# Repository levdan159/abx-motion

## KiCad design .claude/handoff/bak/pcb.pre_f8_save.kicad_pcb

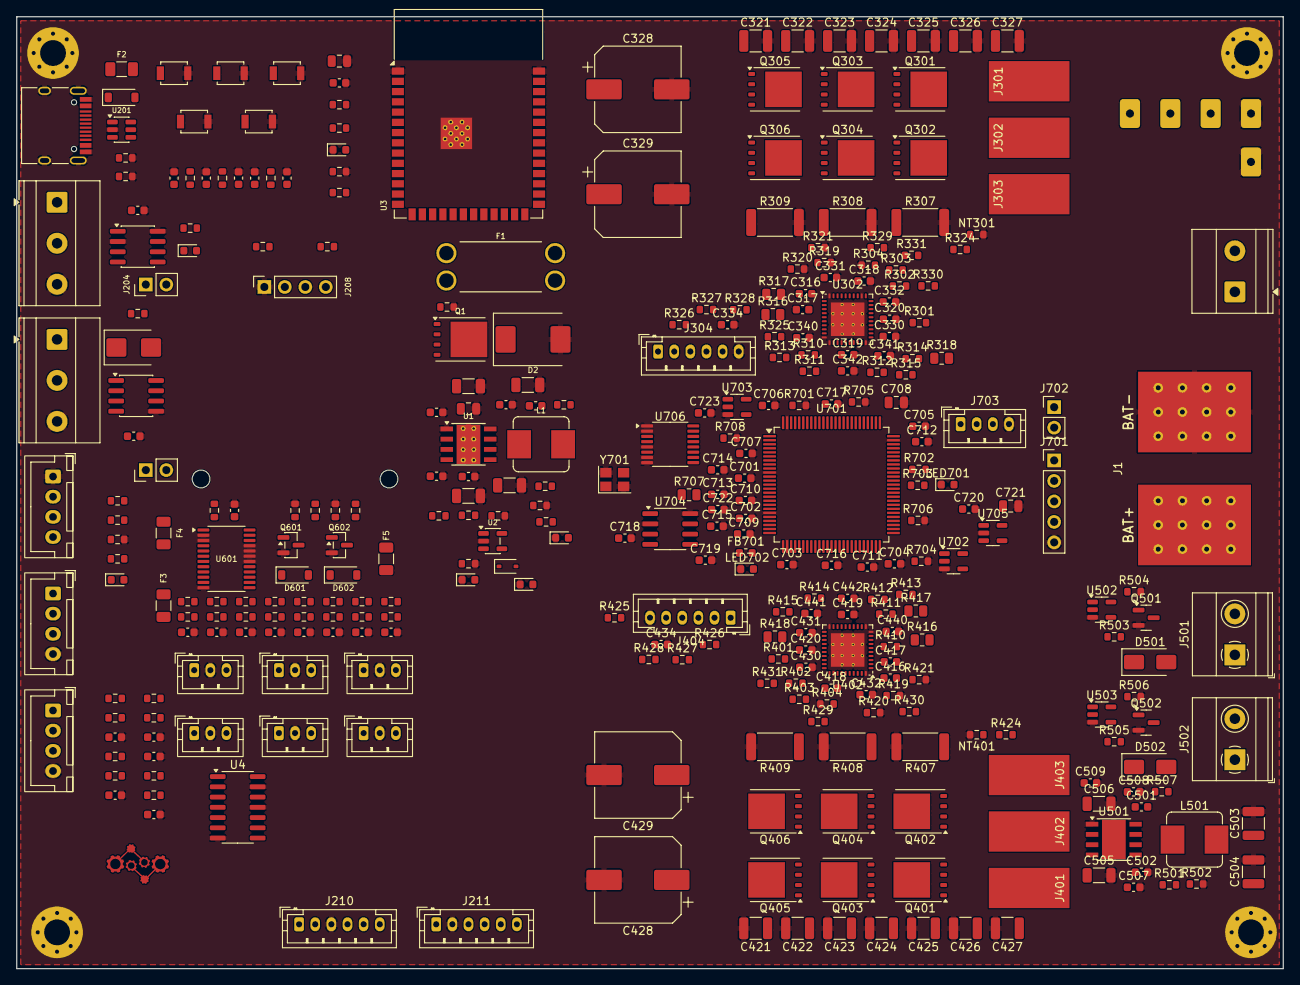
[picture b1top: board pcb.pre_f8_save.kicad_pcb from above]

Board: 4 copper layers, 157.0 x 118.0 mm, 344 parts (1 on the bottom side), 224 nets, no tracks yet.

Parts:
C1, C6, C202, C203, C204, C209, C210, C211, C212, C213, C214, C319, C419, C501, C508, C509, C601, C701, C702, C703, C704, C705, C706, C707, C709, C715, C716, C717, C718, C719, C722, C723: 100nF; C_0603_1608Metric
C2, C3, C505, C506: 4.7uF/100V; C_1206_3216Metric
C4, C320, C420, C507: 100nF/100V; C_0603_1608Metric
C5, C9, C318, C418, C502, C710, C720: 1uF; C_0603_1608Metric
C7, C8: 22uF; C_1206_3216Metric
C10, C201, C721: 10uF; C_0805_2012Metric
C205, C206, C207, C208, C340, C341, C342, C440, C441, C442: 1nF; C_0603_1608Metric
C316, C416: 47nF/100V; C_0603_1608Metric
C317, C417: 1uF/25V; C_0603_1608Metric
C321, C322, C323, C324, C325, C326, C327, C421, C422, C423, C424, C425, C426, C427: 10uF/100V; C_1210_3225Metric
C328, C329, C428, C429: 220uF/63V; CP_Elec_10x10.5
C330, C331, C332, C430, C431, C432: 2.2nF; C_0603_1608Metric
C334, C434, C602, C603, C604, C605, C606, C607, C608, C609: 10nF; C_0603_1608Metric
C503, C504: 22uF/50V; C_1210_3225Metric
C708: 4.7uF; C_0805_2012Metric
C711, C712: 2.2uF; C_0603_1608Metric
C713, C714: 18pF; C_0603_1608Metric
D1: BZT52C12S; D_SOD-323
D2: SMCJ43A; D_SMC
D201: SMBJ6.5CA; D_SMB
D202, D601, D602: B5819W; D_SOD-123
D501, D502: SS34; D_SMA
F1: 5A; Fuseholder_Keystone_3557-2
F2, F3, F5: 500mA_PTC; Fuse_1206_3216Metric
F4: 250mA_PTC; Fuse_1206_3216Metric
FB701: 600R@100MHz; L_0603_1608Metric
H1, H2, H3, H4: M3_Mount; MountingHole_3.2mm_M3_Pad_Via
H5, H6: M2_OLED; MountingHole_2.2mm_M2
J1: BATTERY_IN; ABX_BatteryPads_1x02_SMD_10x14mm_P14mm
J102: E_STOP; TerminalBlock_Phoenix_MKDS-1,5-2-5.08_1x02_P5.08mm_Horizont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
J201: USB-C; USB_C_Receptacle_HRO_TYPE-C-31-M-12
J202: ENC1_CONN; JST_XH_B4B-XH-A_1x04_P2.50mm_Vertical
J203: ENC2_CONN; JST_XH_B4B-XH-A_1x04_P2.50mm_Vertical
J204: CAN_TERM; PinHeader_1x02_P2.54mm_Vertical
J205: CAN_BUS; TerminalBlock_Phoenix_MKDS-1,5-3-5.08_1x03_P5.08mm_Horizont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
J206: RS485_TERM; PinHeader_1x02_P2.54mm_Vertical
J207: RS485_BUS; TerminalBlock_Phoenix_MKDS-1,5-3-5.08_1x03_P5.08mm_Horizont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
J208: OLED_I2C; PinSocket_1x04_P2.54mm_Vertical
J209: I2C_EXP; JST_XH_B4B-XH-A_1x04_P2.50mm_Vertical
J210: GPS; JST_PH_B6B-PH-K_1x06_P2.00mm_Vertical
J211: IMU; JST_PH_B6B-PH-K_1x06_P2.00mm_Vertical
J301, J401: PHASE_A; SolderWirePad_1x01_SMD_5x10mm
J302, J402: PHASE_B; SolderWirePad_1x01_SMD_5x10mm
J303, J403: PHASE_C; SolderWirePad_1x01_SMD_5x10mm
J304, J404: HALL_TEMP; JST_PH_B6B-PH-K_1x06_P2.00mm_Vertical
J501: BRAKE1; TerminalBlock_Phoenix_MKDS-1,5-2-5.08_1x02_P5.08mm_Horizont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
J502: BRAKE2; TerminalBlock_Phoenix_MKDS-1,5-2-5.08_1x02_P5.08mm_Horizont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
J601, J602, J603, J604, J605, J606: B3B-PH-K-S; JST_PH_B3B-PH-K_1x03_P2.00mm_Vertical
J701: SWD; PinHeader_1x05_P2.54mm_Vertical
J702: BOOT; PinHeader_1x02_P2.54mm_Vertical
J703: UART; JST_PH_B4B-PH-K_1x04_P2.00mm_Vertical
L1: 15uH; L_Bourns_SRP7028A_7.3x6.6mm
L501: 47uH 3A; L_Bourns_SRP7028A_7.3x6.6mm
LED201: LED_YEL_CAN; LED_0603_1608Metric
LED202: LED_YEL_485; LED_0603_1608Metric
LED203: LED_BLU_STAT; LED_0603_1608Metric
LED701: LED_GRN; LED_0603_1608Metric
LED702: LED_RED; LED_0603_1608Metric
LED_PWR_3V3_1, LED_PWR_5V1: LED_GRN; LED_0603_1608Metric
LED_PWR_BATT1: LED_GRN; LED_0603_1608Metric
LOGO1: ABX_Logo_Gears_Gold
LOGO2: ABX_Text_Gold
NT301, NT401: NTC 10k B3435; R_0603_1608Metric
Q1: SQJ459EP-T1_GE3; TDSON-8-1
Q301, Q302, Q303, Q304, Q305, Q306, Q401, Q402, Q403, Q404, Q405, Q406: CSD19532Q5B; TDSON-8-1
Q501, Q502: SI2318CDS; SOT-23
Q601, Q602: AO3400A; SOT-23
R1: 47k; R_0603_1608Metric
R2, R4, R501, R504, R506, R706: 100k; R_0603_1608Metric
R3: 6.8k; R_0603_1608Metric
R5: 24.9k; R_0603_1608Metric
R6: 22k; R_0603_1608Metric
R7, R8, R212, R214, R216, R218, R220, R224, R230, R326, R327, R328, R426, R427, R428, R507, R609, R610, R611, R612, R613, R614, R615, R616, R617, R618, R702, R703: 1k; R_0603_1608Metric
R9, R203, R206, R227, R228, R229, R231, R232, R301, R302, R303, R304, R324, R325, R401, R402, R403, R404, R424, R425, R701, R704, R705: 10k; R_0603_1608Metric
R201, R202: 5.1k; R_0603_1608Metric
R211, R213, R215, R217, R225, R226, R329, R330, R331, R429, R430, R431, R601, R602, R603, R604, R605, R606, R607, R608: 4.7k; R_0603_1608Metric
R219, R221: 120; R_0603_1608Metric
R222, R223: 330R; R_0603_1608Metric
R307, R308, R309, R407, R408, R409: 1m 3W; R_2512_6332Metric
R310, R311, R312, R313, R314, R315, R410, R411, R412, R413, R414, R415: 2.2; R_0603_1608Metric
R316, R317, R318, R416, R417, R418, R707: 39k; R_0805_2012Metric
R319, R320, R321, R419, R420, R421, R708: 2.2k; R_0603_1608Metric
R502: 4.32k; R_0603_1608Metric
R503, R505: 22; R_0603_1608Metric
R619, R620: 100; R_0603_1608Metric
SW201: RESET; SW_SPST_B3U-1000P
SW202: BOOT; SW_SPST_B3U-1000P
SW203: BTN_BACK; SW_SPST_B3U-1000P
SW204: BTN_NEXT; SW_SPST_B3U-1000P
SW205: BTN_HOME; SW_SPST_B3U-1000P
TP_3V3_1: TP_3V3_1; TestPoint_Pad_D1.5mm
TP_5V1: TP_5V1; TestPoint_Pad_D1.5mm
TP_BATT1: TP_BATT1; TestPoint_Pad_D1.5mm
TP_GND1: TP_GND1; TestPoint_Pad_D1.5mm
TP_GND2: TP_GND2; TestPoint_Pad_D1.5mm
U1: LMR36520FADDA; Texas_HSOP-8-1EP_3.9x4.9mm_P1.27mm_ThermalVias
U2, U705: AP2112K-3.3; SOT-23-5
U3: ESP32-S3-WROOM-1-N8R2; ESP32-S3-WROOM-1
U4: 74LVC14A; SOIC-14_3.9x8.7mm_P1.27mm
U201: USBLC6-2SC6; SOT-23-6
U202: TCAN1042V-Q1; SOIC-8_3.9x4.9mm_P1.27mm
U203: THVD1450DR; SOIC-8_3.9x4.9mm_P1.27mm
U302, U402: DRV8323SRTAR; Texas_RTA0040B_WQFN-40-1EP_6x6mm_P0.5mm_EP4.15x4.15mm
U501: LMR36520FADDA; Texas_HSOP-8-1EP_3.9x4.9mm_P1.27mm
U502, U503, U702, U703: 74LVC1G08; SOT-23-5
U601: PCA9555PW,118; TSSOP-24_4.4x7.8mm_P0.65mm
U701: STM32F405VGT6; LQFP-100_14x14mm_P0.5mm
U704: TCAN1042V; SOIC-8_3.9x4.9mm_P1.27mm
U706: 74HC4051; TSSOP-16_4.4x5mm_P0.65mm
Y701: 8MHz CL12pF; Crystal_SMD_3225-4Pin_3.2x2.5mm

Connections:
+3V3: C10.1, C201.1, C202.1, C209.1, C211.1, C508.1, C509.1, C601.1, F4.1, J102.1, J208.2, J210.2, J211.1, R8.1, R203.1, R206.1, R220.1, R222.1, R224.1, R225.1, R226.1, R227.1, R228.1, R229.1, R232.1, R601.1, R602.1, R603.1, R604.1, R605.1, R606.1, R607.1, R608.1, TP_3V3_1.1 (1_1), U2.5 (VOUT), U3.2 (3V3), U4.14 (VCC), U202.5 (VIO), U203.8 (VCC), U502.5 (VCC), U503.5 (VCC), U601.24 (VDD)
+3V3_ESC: C319.1, C419.1, C701.1, C702.1, C703.1, C704.1, C705.1, C706.1, C707.1, C708.1, C716.1, C717.1, C719.1, C721.1, C723.1, FB701.1, J701.1, J702.2, R301.1, R302.1, R303.1, R324.1, R325.1, R329.1, R330.1, R331.1, R401.1, R402.1, R403.1, R424.1, R425.1, R429.1, R430.1, R431.1, U302.24 (VREF), U402.24 (VREF), U701.6 (VBAT), U701.11 (VDD), U701.19 (VDD), U701.28 (VDD), U701.50 (VDD), U701.75 (VDD), U701.100 (VDD), U702.5 (VCC), U703.5 (VCC), U704.5 (VIO), U705.5 (VOUT), U706.16 (VCC)
+5V: C7.1, C8.1, C9.1, C210.1, C718.1, C720.1, D202.1 (K), F3.1, F5.1, J210.1, J304.1, J404.1, J703.1, L1.2, R4.1, R7.1, R211.1, R213.1, R215.1, R217.1, TP_5V1.1 (1_1), U2.1 (VIN), U2.3 (EN), U202.3 (VCC), U704.3 (VCC), U705.1 (VIN), U705.3 (EN)
+BATT: C2.1, C3.1, C4.1, C505.1, C506.1, C507.1, D1.1 (K), D2.1 (A1), Q1.1 (S), Q1.2 (S), Q1.3 (S), R2.1, R6.1, TP_BATT1.1 (1_1), U1.2 (VIN), U1.3 (EN), U501.2 (VIN), U501.3 (EN)
/+3V3_DRV_EN: J102.2, R9.1, R507.1, R706.1, U502.2, U503.2, U601.17 (IO1_4), U702.2, U703.2
/BRAKE1_EN: U3.19 (IO11), U502.1
/BRAKE2_EN: U3.20 (IO12), U503.1
/Brakes/+24V_BRAKE: C503.1, C504.1, D501.1 (K), D502.1 (K), J501.1, J502.1, L501.2, R501.1
/Brakes/BRK1_COIL_N: D501.2 (A), J501.2, Q501.3 (D)
/Brakes/BRK1_G: R503.1, U502.4
/Brakes/BRK1_GR: Q501.1 (G), R503.2, R504.1
/Brakes/BRK2_COIL_N: D502.2 (A), J502.2, Q502.3 (D)
/Brakes/BRK2_G: R505.1, U503.4
/Brakes/BRK2_GR: Q502.1 (G), R505.2, R506.1
/Brakes/BR_BOOT: C501.1, U501.7 (BOOT)
/Brakes/BR_FB: R501.2, R502.1, U501.5 (FB)
/Brakes/BR_SW: C501.2, L501.1, U501.8 (SW)
/Brakes/BR_VCC: C502.1, U501.6 (VCC)
/CAN_H: J204.1, J205.1, U202.7 (CANH), U704.7 (CANH)
/CAN_L: J205.2, R219.2, U202.6 (CANL), U704.6 (CANL)
/DRV_SCLK: U302.28 (SCLK), U402.28 (SCLK), U701.78 (PC10)
/DRV_SDI: U302.27 (SDI), U402.27 (SDI), U701.80 (PC12)
/DRV_SDO: R302.2, R402.2, U302.26 (SDO), U402.26 (SDO), U701.79 (PC11)
/ESC_MCU/ADC_MUX: U701.29 (PA4), U706.3 (A)
/ESC_MCU/BOOT0: J702.1, R701.1, U701.94 (BOOT0)
/ESC_MCU/CAN_RX: U701.81 (PD0), U704.4 (RXD)
/ESC_MCU/CAN_TX: U701.82 (PD1), U704.1 (TXD)
/ESC_MCU/LED_G: R702.1, U701.66 (PC9)
/ESC_MCU/LED_G_A: LED701.2 (A), R702.2
/ESC_MCU/LED_R: R703.1, U701.67 (PA8)
/ESC_MCU/LED_R_A: LED702.2 (A), R703.2
/ESC_MCU/M1_EN_MCU: R704.1, U701.45 (PE14), U702.1
/ESC_MCU/M2_EN_MCU: R705.1, U701.85 (PD4), U703.1
/ESC_MCU/MUX_EN_N: U701.51 (PB12), U706.6 (~E)
/ESC_MCU/MUX_S0: U701.88 (PD7), U706.11 (S0)
/ESC_MCU/MUX_S1: U701.89 (PB3), U706.10 (S1)
/ESC_MCU/MUX_S2: U701.38 (PE7), U706.9 (S2)
/ESC_MCU/OSC_IN: C713.1, U701.12 (PH0), Y701.1
/ESC_MCU/OSC_OUT: C714.1, U701.13 (PH1), Y701.3
/ESC_MCU/SWCLK: J701.3, U701.76 (PA14)
/ESC_MCU/SWDIO: J701.2, U701.72 (PA13)
/ESC_MCU/UART_RX: J703.3, U701.48 (PB11)
/ESC_MCU/UART_TX: J703.2, U701.47 (PB10)
/ESC_MCU/VCAP1: C711.1, U701.49 (VCAP_1)
/ESC_MCU/VCAP2: C712.1, U701.73 (VCAP_2)
/ESC_MCU/VDDA_ESC: C709.1, C710.1, FB701.2, U701.21 (VREF+), U701.22 (VDDA)
/ESC_MCU/VIN_SENS: C722.1, R707.2, R708.1, U701.15 (PC0), U701.26 (PA3), U706.4 (A7)
/ESC_Motor_1/CAL: R304.2, U302.31 (CAL)
/ESC_Motor_1/CPH: C316.1, U302.2 (CPH)
/ESC_Motor_1/CPL: C316.2, U302.1 (CPL)
/ESC_Motor_1/DVDD: C318.1, U302.33 (DVDD)
/ESC_Motor_1/GHA: R310.1, U302.6 (GHA)
/ESC_Motor_1/GHA_G: Q301.4 (G), R310.2
/ESC_Motor_1/GHB: R312.1, U302.15 (GHB)
/ESC_Motor_1/GHB_G: Q303.4 (G), R312.2
/ESC_Motor_1/GHC: R314.1, U302.16 (GHC)
/ESC_Motor_1/GHC_G: Q305.4 (G), R314.2
/ESC_Motor_1/GLA: R311.1, U302.8 (GLA)
/ESC_Motor_1/GLA_G: Q302.4 (G), R311.2
/ESC_Motor_1/GLB: R313.1, U302.13 (GLB)
/ESC_Motor_1/GLB_G: Q304.4 (G), R313.2
/ESC_Motor_1/GLC: R315.1, U302.18 (GLC)
/ESC_Motor_1/GLC_G: Q306.4 (G), R315.2
/ESC_Motor_1/HALL1_IN: J304.2, R326.1
/ESC_Motor_1/HALL2_IN: J304.3, R327.1
/ESC_Motor_1/HALL3_IN: J304.4, R328.1
/ESC_Motor_1/PH_A: J301.1 (Pin_1_1), Q301.1 (S), Q301.2 (S), Q301.3 (S), Q302.5 (D), R316.1, U302.7 (SHA)
/ESC_Motor_1/PH_B: J302.1 (Pin_1_1), Q303.1 (S), Q303.2 (S), Q303.3 (S), Q304.5 (D), R317.1, U302.14 (SHB)
/ESC_Motor_1/PH_C: J303.1 (Pin_1_1), Q305.1 (S), Q305.2 (S), Q305.3 (S), Q306.5 (D), R318.1, U302.17 (SHC)
/ESC_Motor_1/SPA: Q302.1 (S), Q302.2 (S), Q302.3 (S), R307.1, U302.9 (SPA)
/ESC_Motor_1/SPB: Q304.1 (S), Q304.2 (S), Q304.3 (S), R308.1, U302.12 (SPB)
/ESC_Motor_1/SPC: Q306.1 (S), Q306.2 (S), Q306.3 (S), R309.1, U302.19 (SPC)
/ESC_Motor_1/VCP: C317.1, U302.3 (VCP)
/ESC_Motor_2/CAL: R404.2, U402.31 (CAL)
/ESC_Motor_2/CPH: C416.1, U402.2 (CPH)
/ESC_Motor_2/CPL: C416.2, U402.1 (CPL)
/ESC_Motor_2/DVDD: C418.1, U402.33 (DVDD)
/ESC_Motor_2/GHA: R410.1, U402.6 (GHA)
/ESC_Motor_2/GHA_G: Q401.4 (G), R410.2
/ESC_Motor_2/GHB: R412.1, U402.15 (GHB)
/ESC_Motor_2/GHB_G: Q403.4 (G), R412.2
/ESC_Motor_2/GHC: R414.1, U402.16 (GHC)
/ESC_Motor_2/GHC_G: Q405.4 (G), R414.2
/ESC_Motor_2/GLA: R411.1, U402.8 (GLA)
/ESC_Motor_2/GLA_G: Q402.4 (G), R411.2
/ESC_Motor_2/GLB: R413.1, U402.13 (GLB)
/ESC_Motor_2/GLB_G: Q404.4 (G), R413.2
/ESC_Motor_2/GLC: R415.1, U402.18 (GLC)
/ESC_Motor_2/GLC_G: Q406.4 (G), R415.2
/ESC_Motor_2/HALL1_IN: J404.2, R426.1
/ESC_Motor_2/HALL2_IN: J404.3, R427.1
/ESC_Motor_2/HALL3_IN: J404.4, R428.1
/ESC_Motor_2/PH_A: J401.1 (Pin_1_1), Q401.1 (S), Q401.2 (S), Q401.3 (S), Q402.5 (D), R416.1, U402.7 (SHA)
/ESC_Motor_2/PH_B: J402.1 (Pin_1_1), Q403.1 (S), Q403.2 (S), Q403.3 (S), Q404.5 (D), R417.1, U402.14 (SHB)
/ESC_Motor_2/PH_C: J403.1 (Pin_1_1), Q405.1 (S), Q405.2 (S), Q405.3 (S), Q406.5 (D), R418.1, U402.17 (SHC)
/ESC_Motor_2/SPA: Q402.1 (S), Q402.2 (S), Q402.3 (S), R407.1, U402.9 (SPA)
/ESC_Motor_2/SPB: Q404.1 (S), Q404.2 (S), Q404.3 (S), R408.1, U402.12 (SPB)
/ESC_Motor_2/SPC: Q406.1 (S), Q406.2 (S), Q406.3 (S), R409.1, U402.19 (SPC)
/ESC_Motor_2/VCP: C417.1, U402.3 (VCP)
/ESC_NRST: C715.1, J701.4, U3.22 (IO14), U701.14 (NRST)
/ESTOP_SENSE: R507.2, U3.21 (IO13)
/GPS_PPS: J210.6, U3.12 (IO8)
/GPS_RX: J210.4, U3.11 (IO18)
/GPS_TX: J210.5, U3.10 (IO17)
/I2C_SCL: J208.3, J209.3, J211.3, R225.2, U3.35 (IO42), U601.22 (SCL)
/I2C_SDA: J208.4, J209.4, J211.4, R226.2, U3.34 (IO41), U601.23 (SDA)
/IMU_INT: J211.5, U3.4 (IO4)
/IMU_RST: J211.6, U3.5 (IO5)
/IO_INT_N: R206.2, U3.29 (IO36), U601.1 (~INT)
/Industrial_IO/+5V_OUT: D601.1 (K), D602.1 (K), F5.2, J605.1, J606.1
/Industrial_IO/M1_MAX_IN: C603.1, R610.2, U601.5 (IO0_1)
/Industrial_IO/M1_MAX_RAW: J601.3, R602.2, R610.1
/Industrial_IO/M1_MIN_IN: C602.1, R609.2, U601.4 (IO0_0)
/Industrial_IO/M1_MIN_RAW: J601.1, R601.2, R609.1
/Industrial_IO/M2_MAX_IN: C605.1, R612.2, U601.7 (IO0_3)
/Industrial_IO/M2_MAX_RAW: J602.3, R604.2, R612.1
/Industrial_IO/M2_MIN_IN: C604.1, R611.2, U601.6 (IO0_2)
/Industrial_IO/M2_MIN_RAW: J602.1, R603.2, R611.1
/Industrial_IO/OUT1_CMD: R617.1, R619.1, U601.13 (IO1_0)
/Industrial_IO/OUT1_GATE: Q601.1 (G), R619.2
/Industrial_IO/OUT1_SW: D601.2 (A), J605.3, Q601.3 (D)
/Industrial_IO/OUT2_CMD: R618.1, R620.1, U601.14 (IO1_1)
/Industrial_IO/OUT2_GATE: Q602.1 (G), R620.2
/Industrial_IO/OUT2_SW: D602.2 (A), J606.3, Q602.3 (D)
/Industrial_IO/S1_MAX_IN: C607.1, R614.2, U601.9 (IO0_5)
/Industrial_IO/S1_MAX_RAW: J603.3, R606.2, R614.1
/Industrial_IO/S1_MIN_IN: C606.1, R613.2, U601.8 (IO0_4)
/Industrial_IO/S1_MIN_RAW: J603.1, R605.2, R613.1
/Industrial_IO/S2_MAX_IN: C609.1, R616.2, U601.11 (IO0_7)
/Industrial_IO/S2_MAX_RAW: J604.3, R608.2, R616.1
/Industrial_IO/S2_MIN_IN: C608.1, R615.2, U601.10 (IO0_6)
/Industrial_IO/S2_MIN_RAW: J604.1, R607.2, R615.1
/M1_ENABLE: U302.30 (ENABLE), U702.4
/M1_HALL1: C340.1, R326.2, R329.2, U701.60 (PD13)
/M1_HALL2: C341.1, R327.2, R330.2, U701.59 (PD12)
/M1_HALL3: C342.1, R328.2, R331.2, U701.61 (PD14)
/M1_INHA: U302.34 (INHA), U701.40 (PE9)
/M1_INHB: U302.36 (INHB), U701.42 (PE11)
/M1_INHC: U302.38 (INHC), U701.44 (PE13)
/M1_INLA: U302.35 (INLA), U701.39 (PE8)
/M1_INLB: U302.37 (INLB), U701.41 (PE10)
/M1_INLC: U302.39 (INLC), U701.43 (PE12)
/M1_SENS_A: C330.1, R316.2, R319.1, U701.25 (PA2)
/M1_SENS_B: C331.1, R317.2, R320.1, U701.23 (PA0)
/M1_SENS_C: C332.1, R318.2, R321.1, U701.24 (PA1)
/M1_SOA: U302.23 (SOA), U701.36 (PB1)
/M1_SOB: U302.22 (SOB), U701.35 (PB0)
/M1_SOC: U302.21 (SOC), U701.33 (PC4)
/M1_TEMP_MOS: NT301.1, R324.2, U706.13 (A0)
/M1_TEMP_MOT: C334.1, J304.5, R325.2, U706.15 (A2)
/M1_nFAULT: R301.2, U302.25 (nFAULT), U701.2 (PE3)
/M1_nSCS: R303.2, U302.29 (nSCS), U701.7 (PC13)
/M2_ENABLE: U402.30 (ENABLE), U703.4
/M2_HALL1: C440.1, R426.2, R429.2, U701.90 (PB4)
/M2_HALL2: C441.1, R427.2, R430.2, U701.92 (PB6)
/M2_HALL3: C442.1, R428.2, R431.2, U701.93 (PB7)
/M2_INHA: U402.34 (INHA), U701.63 (PC6)
/M2_INHB: U402.36 (INHB), U701.64 (PC7)
/M2_INHC: U402.38 (INHC), U701.65 (PC8)
/M2_INLA: U402.35 (INLA), U701.32 (PA7)
/M2_INLB: U402.37 (INLB), U701.53 (PB14)
/M2_INLC: U402.39 (INLC), U701.54 (PB15)
/M2_SENS_A: C430.1, R416.2, R419.1, U701.18 (PC3)
/M2_SENS_B: C431.1, R417.2, R420.1, U701.17 (PC2)
/M2_SENS_C: C432.1, R418.2, R421.1, U701.16 (PC1)
/M2_SOA: U402.23 (SOA), U701.34 (PC5)
/M2_SOB: U402.22 (SOB), U701.31 (PA6)
/M2_SOC: U402.21 (SOC), U701.30 (PA5)
/M2_TEMP_MOS: NT401.1, R424.2, U706.14 (A1)
/M2_TEMP_MOT: C434.1, J404.5, R425.2, U706.12 (A3)
/M2_nFAULT: R401.2, U402.25 (nFAULT), U701.84 (PD3)
/M2_nSCS: R403.2, U402.29 (nSCS), U701.83 (PD2)
/MCU_and_Encoders/+3V3_EXT: F4.2, J209.2
/MCU_and_Encoders/+5V_ENC: F3.2, J202.1, J203.1
/MCU_and_Encoders/BTN_BACK: C212.1, R227.2, SW203.1, U3.23 (IO21)
/MCU_and_Encoders/BTN_HOME: C214.1, R229.2, SW205.1, U3.33 (IO40)
/MCU_and_Encoders/BTN_NEXT: C213.1, R228.2, SW204.1, U3.30 (IO37)
/MCU_and_Encoders/CAN_LED_A: LED201.2 (A), R220.2
/MCU_and_Encoders/CAN_RX: U3.32 (IO39), U202.4 (RXD)
/MCU_and_Encoders/CAN_TERM_SW: J204.2, R219.1
/MCU_and_Encoders/CAN_TX: LED201.1 (K), R232.2, U3.31 (IO38), U202.1 (TXD)
/MCU_and_Encoders/ENC1_A: U3.8 (IO15), U4.2
/MCU_and_Encoders/ENC1_A_FILT: C205.1, R212.2, U4.1
/MCU_and_Encoders/ENC1_A_RAW: J202.2, R211.2, R212.1
/MCU_and_Encoders/ENC1_B: U3.9 (IO16), U4.4
/MCU_and_Encoders/ENC1_B_FILT: C206.1, R214.2, U4.3
/MCU_and_Encoders/ENC1_B_RAW: J202.3, R213.2, R214.1
/MCU_and_Encoders/ENC2_A: U3.17 (IO9), U4.6
/MCU_and_Encoders/ENC2_A_FILT: C207.1, R216.2, U4.5
/MCU_and_Encoders/ENC2_A_RAW: J203.2, R215.2, R216.1
/MCU_and_Encoders/ENC2_B: U3.18 (IO10), U4.8
/MCU_and_Encoders/ENC2_B_FILT: C208.1, R218.2, U4.9
/MCU_and_Encoders/ENC2_B_RAW: J203.3, R217.2, R218.1
/MCU_and_Encoders/ESP_BOOT: C204.1, SW202.1, U3.27 (IO0)
/MCU_and_Encoders/ESP_EN: C203.1, R203.2, SW201.1, U3.3 (EN)
/MCU_and_Encoders/LED_STAT: R230.1, U3.15 (IO3)
/MCU_and_Encoders/RS485_A: D201.1 (A1), J206.1, J207.1, R222.2, U203.6 (A)
/MCU_and_Encoders/RS485_B: D201.2 (A2), J207.2, R221.2, R223.1, U203.7 (B)
/MCU_and_Encoders/RS485_DIR: R231.1, U3.28 (IO35), U203.2 (~RE), U203.3 (DE)
/MCU_and_Encoders/RS485_LED_A: LED202.2 (A), R224.2
/MCU_and_Encoders/RS485_RX: U3.36 (RXD0), U203.1 (RO)
/MCU_and_Encoders/RS485_TERM_SW: J206.2, R221.1
/MCU_and_Encoders/RS485_TX: LED202.1 (K), U3.37 (TXD0), U203.4 (DI)
/MCU_and_Encoders/STAT_LED_A: LED203.2 (A), R230.2
/MCU_and_Encoders/USB_CC1: J201.A5 (CC1), R201.1
/MCU_and_Encoders/USB_CC2: J201.B5 (CC2), R202.1
/MCU_and_Encoders/USB_CONN_DN: J201.A7 (D-), J201.B7 (D-), U201.1 (I/O1)
/MCU_and_Encoders/USB_CONN_DP: J201.A6 (D+), J201.B6 (D+), U201.3 (I/O2)
/MCU_and_Encoders/USB_DN: U3.13 (USB_D-), U201.6 (I/O1)
/MCU_and_Encoders/USB_DP: U3.14 (USB_D+), U201.4 (I/O2)
/MCU_and_Encoders/VBUS_FUSED: D202.2 (A), F2.2
/MCU_and_Encoders/VBUS_USB: F2.1, J201.A4 (VBUS), J201.A9 (VBUS), J201.B4 (VBUS), J201.B9 (VBUS), U201.5 (VBUS)
/Power_Supply/3V3_LED_A: LED_PWR_3V3_1.2 (A), R8.2
/Power_Supply/5V_LED_A: LED_PWR_5V1.2 (A), R7.2
/Power_Supply/BATT_LED_A: LED_PWR_BATT1.2 (A), R6.2
/Power_Supply/Q1_GATE: D1.2 (A), Q1.4 (G), R1.1
/Power_Supply/U1_BOOT: C6.1, U1.7 (BOOT)
/Power_Supply/U1_FB: R4.2, R5.1, U1.5 (FB)
/Power_Supply/U1_SW: C6.2, L1.1, U1.8 (SW)
/Power_Supply/U1_VCC: C5.1, U1.6 (VCC)
/Power_Supply/V_FUSED: F1.2, Q1.5 (D)
/VBAT_SENSE: C1.1, R2.2, R3.1, U3.39 (IO1)
GND: C1.2, C2.2, C3.2, C4.2, C5.2, C7.2, C8.2, C9.2, C10.2, C201.2, C202.2, C203.2, C204.2, C205.2, C206.2, C207.2, C208.2, C209.2, C210.2, C211.2, C212.2, C213.2, C214.2, C318.2, C319.2, C320.2, C321.2, C322.2, C323.2, C324.2, C325.2, C326.2, C327.2, C328.2, C329.2, C330.2, C331.2, C332.2, C334.2, C340.2, C341.2, C342.2, C418.2, C419.2, C420.2, C421.2, C422.2, C423.2, C424.2, C425.2, C426.2, C427.2, C428.2, C429.2, C430.2, C431.2, C432.2, C434.2, C440.2, C441.2, C442.2, C502.2, C503.2, C504.2, C505.2, C506.2, C507.2, C508.2, C509.2, C601.2, C602.2, C603.2, C604.2, C605.2, C606.2, C607.2, C608.2, C609.2, C701.2, C702.2, C703.2, C704.2, C705.2, C706.2, C707.2, C708.2, C709.2, C710.2, C711.2, C712.2, C713.2, C714.2, C715.2, C716.2, C717.2, C718.2, C719.2, C720.2, C721.2, C722.2, C723.2, D2.2 (A2), H1.1 (1_1), H2.1 (1_1), H3.1 (1_1), H4.1 (1_1), J1.2, J201.A1 (GND), J201.A12 (GND), J201.B1 (GND), J201.B12 (GND), J201.S1 (SHIELD), J202.4, J203.4, J205.3, J207.3, J208.1, J209.1, J210.3, J211.2, J304.6, J404.6, J601.2, J602.2, J603.2, J604.2, J605.2, J606.2, J701.5, J703.4, LED203.1 (K), LED701.1 (K), LED702.1 (K), LED_PWR_3V3_1.1 (K), LED_PWR_5V1.1 (K), LED_PWR_BATT1.1 (K), NT301.2, NT401.2, Q501.2 (S), Q502.2 (S), Q601.2 (S), Q602.2 (S), R1.2, R3.2, R5.2, R9.2, R201.2, R202.2, R223.2, R231.2, R304.1, R307.2, R308.2, R309.2, R319.2, R320.2, R321.2, R404.1, R407.2, R408.2, R409.2, R419.2, R420.2, R421.2, R502.2, R504.2, R506.2, R617.2, R618.2, R701.2, R704.2, R705.2, R706.2, R708.2, SW201.2, SW202.2, SW203.2, SW204.2, SW205.2, TP_GND1.1 (1_1), TP_GND2.1 (1_1), U1.1 (GND), U1.9 (GND), U2.2 (GND), U3.1 (GND), U3.40 (GND), U3.41 (GND), U4.7 (GND), U4.11, U4.13, U201.2 (GND), U202.2 (GND), U202.8 (STB), U203.5 (GND), U302.10 (SNA), U302.11 (SNB), U302.20 (SNC), U302.32 (AGND), U302.40 (PGND), U302.41 (PAD), U402.10 (SNA), U402.11 (SNB), U402.20 (SNC), U402.32 (AGND), U402.40 (PGND), U402.41 (PAD), U501.1 (GND), U501.9 (GND), U502.3 (GND), U503.3 (GND), U601.2 (A1), U601.3 (A2), U601.12 (VSS), U601.18 (IO1_5), U601.19 (IO1_6), U601.20 (IO1_7), U601.21 (A0), U701.10 (VSS), U701.20 (VSSA), U701.27 (VSS), U701.74 (VSS), U701.99 (VSS), U702.3 (GND), U703.3 (GND), U704.2 (GND), U704.8 (STB), U705.2 (GND), U706.1 (A4), U706.2 (A6), U706.5 (A5), U706.7 (VEE), U706.8 (GND), Y701.2, Y701.4
VBUS: C317.2, C320.1, C321.1, C322.1, C323.1, C324.1, C325.1, C326.1, C327.1, C328.1, C329.1, C417.2, C420.1, C421.1, C422.1, C423.1, C424.1, C425.1, C426.1, C427.1, C428.1, C429.1, F1.1, J1.1, Q301.5 (D), Q303.5 (D), Q305.5 (D), Q401.5 (D), Q403.5 (D), Q405.5 (D), R707.1, U302.4 (VM), U302.5 (VDRAIN), U402.4 (VM), U402.5 (VDRAIN)

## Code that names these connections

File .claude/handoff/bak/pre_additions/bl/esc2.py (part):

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c('C316', '47nF/100V', 200, 110, 'CPH', 'CPL'); c('C317', '1uF/25V', 212, 110, 'VCP', 'VBUS'); c('C318', '1uF', 224, 110, 'DVDD', 'GND')
c('C319', '100nF', 236, 110, '+3V3_ESC', 'GND'); c('C320', '100nF/100V', 248, 110, 'VBUS', 'GND'); c('C321', '10uF/100V', 260, 110, 'VBUS', 'GND', C12)
r('R301', '10k', 276, 110, '+3V3_ESC', 'hier:nFAULT'); r('R302', '10k', 286, 110, '+3V3_ESC', 'hier:SDO'); r('R303', '10k', 296, 110, '+3V3_ESC', 'hier:nSCS'); r('R304', '10k', 306, 110, 'GND', 'CAL')
sh.text('VM: 100nF + 10uF within 3 mm of pin 4; CPH-CPL 47nF rated VM; VCP-VM 1uF/25V', 195, 100, 1.4)
for ph, x0, q_h, q_l, rg_h, rg_l, rs, jn in (('A', 370, 'Q301', 'Q302', 'R310', 'R311', 'R307', 'J301'), ('B', 450, 'Q303', 'Q304', 'R312', 'R313', 'R308', 'J302'), ('C', 530, 'Q305', 'Q306', 'R314', 'R315', 'R309', 'J303')):
    FET, TD = 'Transistor_FET:CSD19532Q5B', 'Package_TO_SOT_SMD:TDSON-8-1'
    add(q_h, FET, 'CSD19532Q5B', TD, x0, 170, {'1': f'PH_{ph}', '2': f'PH_{ph}', '3': f'PH_{ph}', '4': f'GH{ph}_G', '5': 'VBUS'})
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m.globals.update({'BUS_FLT_N', 'BUS_IMON'})   # Bus_Breaker global labels (were ESP32 IO48 / IO6)
m.text('ESC MCU - one STM32F405VGT6 runs both motors (VESC firmware, HW_HAS_DUAL_MOTORS)', 20, 20, 3.5, True)
m.text('Pin map = hwconf/stormcore/60D (HW_VER_IS_60D: CURRENT_AMP_GAIN 10, CURRENT_SHUNT_RES 0.001, VIN 39k/2.2k). Own hwconf: copy hw_stormcore_60d_core.*, drop the smart switch (HW_EARLY_INIT, SWITCH_*), NRF, IMU and RGB LED.', 20, 28, 1.8)
m.text('Motor 1 = TIM1 (PE8-PE13), CURR1-3 PB1/PB0/PC4, SENS1-3 PA2/PA0/PA1, halls PD13/PD12/PD14 (+ABI encoder option on TIM4), nSCS PC13, EN PE14, nFAULT PE3', 20, 34, 1.8)
m.text('Ex-ESP32 signals (ESP32 sheets removed 2026-10-24): PE5/PE6 = BRAKE1_EN/BRAKE2_EN (TIM9 CH1/CH2, brake PWM), PD10 = ESTOP_SENSE (in), PD8 = BUS_FLT_N (in), PA11/PA12 = USB D-/D+, PA9 = USB VBUS sense', 20, 46, 1.8)
m.text('Motor 2 = TIM8 (PC6-8, PA7, PB14, PB15), CURR4-6 PC5/PA6/PA5, SENS4-6 PC3/PC2/PC1, halls PB4/PB6/PB7, nSCS PD2, EN PD4, nFAULT PD3. Shared DRV SPI (bit-bang): SCK PC10, MISO PC11, MOSI PC12', 20, 40, 1.8)
st = {'PE9': 'hier:M1_INHA', 'PE8': 'hier:M1_INLA', 'PE11': 'hier:M1_INHB', 'PE10': 'hier:M1_INLB', 'PE13': 'hier:M1_INHC', 'PE12': 'hier:M1_INLC',
      'PC6': 'hier:M2_INHA', 'PA7': 'hier:M2_INLA', 'PC7': 'hier:M2_INHB', 'PB14': 'hier:M2_INLB', 'PC8': 'hier:M2_INHC', 'PB15': 'hier:M2_INLC',
      'PE14': 'M1_EN_MCU', 'PD4': 'M2_EN_MCU', 'PE3': 'hier:M1_nFAULT', 'PD3': 'hier:M2_nFAULT',
      'PC10': 'hier:DRV_SCLK', 'PC11': 'hier:DRV_SDO', 'PC12': 'hier:DRV_SDI', 'PC13': 'hier:M1_nSCS', 'PD2': 'hier:M2_nSCS',
      'PB1': 'hier:M1_SOA', 'PB0': 'hier:M1_SOB', 'PC4': 'hier:M1_SOC', 'PC5': 'hier:M2_SOA', 'PA6': 'hier:M2_SOB', 'PA5': 'hier:M2_SOC',
      'PA2': 'hier:M1_SENS_A', 'PA0': 'hier:M1_SENS_B', 'PA1': 'hier:M1_SENS_C', 'PC3': 'hier:M2_SENS_A', 'PC2': 'hier:M2_SENS_B', 'PC1': 'hier:M2_SENS_C',
      'PC0': 'VIN_SENS', 'PA3': 'VIN_SENS', 'PA4': 'ADC_MUX', 'PB12': 'MUX_EN_N', 'PD7': 'MUX_S0', 'PB3': 'MUX_S1', 'PE7': 'MUX_S2',
      'PD13': 'hier:M1_HALL1', 'PD12': 'hier:M1_HALL2', 'PD14': 'hier:M1_HALL3', 'PB4': 'hier:M2_HALL1', 'PB6': 'hier:M2_HALL2', 'PB7': 'hier:M2_HALL3',
      'PE15': 'ESTOP_OK', 'PD0': 'CAN_RX', 'PD1': 'CAN_TX', 'PB10': 'UART_TX', 'PB11': 'UART_RX', 'PC9': 'LED_G', 'PA8': 'LED_R',
      'PE5': 'hier:BRAKE1_EN', 'PE6': 'hier:BRAKE2_EN', 'PD10': 'hier:ESTOP_SENSE', 'PD8': 'BUS_FLT_N',   # ex-ESP32 signals (2026-10-24)
      'PA11': 'USB_DM', 'PA12': 'USB_DP', 'PA9': 'USB_VBUS_SNS',
      'PA13': 'SWDIO', 'PA14': 'SWCLK', 'NRST': 'NRST', 'BOOT0': 'BOOT0', 'PH0': 'OSC_IN', 'PH1': 'OSC_OUT',
      'VCAP_1': 'VCAP1', 'VCAP_2': 'VCAP2', 'VBAT': '+3V3_ESC', 'VDDA': 'VDDA_ESC', 'VREF+': 'VDDA_ESC', 'VSSA': 'GND'}
for n in ('11', '19', '28', '50', '75', '100'): st[n] = '+3V3_ESC'
for n in ('10', '27', '74', '99'): st[n] = 'GND'
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add('FB701', 'Device:FerriteBead', '600R@100MHz', 'Inductor_SMD:L_0603_1608Metric', 190, 70, {'1': '+3V3_ESC', '2': 'VDDA_ESC'})
add('#FLG701', 'power:PWR_FLAG', 'PWR_FLAG', '', 205, 70, {'1': 'VDDA_ESC'})
m.text('Decoupling: 100 nF at each of the 6 VDD pins + VBAT, 4.7 uF bulk; VDDA/VREF+ via ferrite; VCAP 2.2 uF each', 30, 58, 1.5)
add('Y701', 'Device:Crystal_GND24', '8MHz CL12pF', 'Crystal:Crystal_SMD_3225-4Pin_3.2x2.5mm', 60, 130, {'1': 'OSC_IN', '3': 'OSC_OUT', '2': 'GND', '4': 'GND'})
c('C713', '18pF', 40, 140, 'OSC_IN', 'GND'); c('C714', '18pF', 80, 140, 'OSC_OUT', 'GND')
c('C715', '100nF', 40, 170, 'NRST', 'GND')
r('R701', '10k', 30, 195, 'BOOT0', 'GND')
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add('U707', '74xGxx:74LVC1G17', '74LVC1G17', 'Package_TO_SOT_SMD:SOT-23-5', 335, 310, {'2': 'DRV_DLY_RC', '4': 'DRV_EN_DLY', '5': '+3V3_ESC', '3': 'GND'}, nc=['1'])
c('C725', '100nF', 350, 300, '+3V3_ESC', 'GND')
r('R710', '1k', 300, 330, 'hier:+3V3_DRV_EN', 'ESTOP_OK')
# temp / aux mux (ADC_IND_ADC_MUX): S2 S1 S0 = PE7 PB3 PD7, /E = PB12
m.text('ADC MUX (Stormcore ADC_SW): 000 MOS1, 001 MOS2, 010 MOT1, 011 MOT2, 100 EXT2 = VBAT_SENSE, 101 EXT1 = BUS_IMON, 110 EXT3, 111 V_BATT', 280, 165, 2, True)
m.text('VBAT_SENSE = +BATT x 6.8k/106.8k (Power R2/R3): 42 V -> 2.67 V, 48 V -> 3.06 V. BUS_IMON = TPS48111 IMON, 30.6 mV/A: 60 A -> 1.84 V; >~105 A (only before the 80 A / 5 ms trip) exceeds 3.3 V, R814 1k limits the clamp current.', 280, 170, 1.4)
add('U706', '74xx:74HC4051', '74HC4051', 'Package_SO:TSSOP-16_4.4x5mm_P0.65mm', 320, 200,
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c('C723', '100nF', 350, 185, '+3V3_ESC', 'GND')
# VBUS sense
r('R707', '39k', 300, 250, 'VBUS', 'VIN_SENS', R08); r('R708', '2.2k', 300, 266, 'VIN_SENS', 'GND'); c('C722', '100nF', 312, 266, 'VIN_SENS', 'GND')
m.text('VIN_SENS 39k/2.2k: 42 V -> 2.2 V. Feeds PC0 (VIN), PA3 (VM) and mux ch7 (V_BATT).', 280, 280, 1.4)
# 3V3 LDO, CAN, UART
m.text('3V3_ESC SUPPLY', 400, 58, 2.5, True)
add('U705', 'Regulator_Linear:AP2112K-3.3', 'AP2112K-3.3', 'Package_TO_SOT_SMD:SOT-23-5', 430, 80, {'VIN': '+5V', 'EN': '+5V', 'GND': 'GND', 'VOUT': '+3V3_ESC'}, nc=['4'])
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# CAN bus terminal + termination (refs/footprints kept from the removed ESP32 sheet so the PCB keeps them)
add('J205', 'Connector:Conn_01x03_Pin', 'CAN_BUS', 'TerminalBlock_Phoenix:TerminalBlock_Phoenix_MKDS-1,5-3-5.08_1x03_P5.08mm_Horizontal', 500, 150,
    {'1': 'CAN_H', '2': 'CAN_L', '3': 'GND'})
add('J204', 'Connector:Conn_01x02_Pin', 'CAN_TERM', 'Connector_PinHeader_2.54mm:PinHeader_1x02_P2.54mm_Vertical', 480, 165, {'1': 'CAN_H', '2': 'CAN_TERM_SW'})
r('R219', '120', 495, 175, 'CAN_TERM_SW', 'CAN_L')
# USB-C (VESC Tool / DFU): OTG_FS PA11 DM / PA12 DP, VBUS sense on PA9 (5 V -> 3.33 V; PA9 is 5 V tolerant). Kept from the ESP32 sheet.
m.text('USB-C (VESC Tool, DFU): STM32 OTG_FS PA11 = D-, PA12 = D+; U201 ESD; R201/R202 5.1k = UFP; F2 + D202 let USB power +5V (bench); PA9 = VBUS sense (R711 10k / R712 20k)', 400, 232, 2, True)
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# ======================= ESP32 sheet: one ESC reset =======================
if os.path.exists(f'{P}/MCU.kicad_sch'):   # ESP32 sheet removed 2026-10-24 (moved to .claude/handoff/bak/pre_esp_removal/)
  t = open(f'{P}/MCU.kicad_sch').read()
  t = t.replace('(hierarchical_label "ESC1_NRST"', '(hierarchical_label "ESC_NRST"')
  for s, e, h in sx.spans(t, 1):
      if h == 'hierarchical_label' and t[s:e].startswith('(hierarchical_label "ESC2_NRST"'):
          x, y = re.search(r'\(at ([-\d.]+) ([-\d.]+)', t[s:e]).groups()
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# MCU block: ESC1_NRST -> ESC_NRST, drop ESC2_NRST
for s, e, h in sx.spans(t, 1):
    if h == 'sheet' and sx.prop(t[s:e], 'Sheetname') == 'MCU_and_Encoders':
        b = t[s:e].replace('(pin "ESC1_NRST"', '(pin "ESC_NRST"')
        for ps, pe, ph in sorted(sx.spans(b, 1), reverse=True):
            if ph == 'pin' and b[ps:pe].startswith('(pin "ESC2_NRST"'): b = cut(b, ps, pe)
        t = t[:s] + b + t[e:]; break
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for k in (1, 2):
    for n in MOT: mp.append((f'M{k}_{n}', m.hier_shapes[f'M{k}_{n}'], 124.46, yy, 180)); yy += 2.54
    yy += 2.54
for i, n in enumerate(['DRV_SCLK', 'DRV_SDI', 'DRV_SDO', None, None, None, '+3V3_DRV_EN', 'BRAKE1_EN', 'BRAKE2_EN', 'ESTOP_SENSE', 'VBAT_SENSE']):   # None: CAN_H/CAN_L/NRST pins dropped 2026-10-24
    if n is None: continue
    mp.append((n, m.hier_shapes.get(n, 'bidirectional'), 175.26, 132.08 + 2.54 * i, 0))
blks += block('ESC_MCU', 'ESC_MCU.kicad_sch', SM, 124.46, 127.0, 50.8, yy - 127.0 + 2.54, mp, '12')
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
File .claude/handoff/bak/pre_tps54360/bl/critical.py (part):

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What it routes (only these):
  1. gate drive per phase: DRV GHx -> R -> high FET gate, GLx -> R -> low FET gate, SHx Kelvin -> high FET source pin
  2. shunt Kelvin pairs SPx/SNx from the inner pad edges of each shunt to the DRV sense pins
  3. DRV local nets: CPH/CPL, VCP, VM (+ VBUS vias), DVDD, VREF (the DRV8323S has no VGLS/AVDD pins)
  4. STM32 crystal Y701 + load caps, VCAP1/2, NRST cap
  5. aux buck U511 (24 V): FB, COMP, CZ, RT, EN, BOOT (12 V buck U512 removed 2026-10-24)
Everything it makes sits in the PCB group 'critical_routes'; a re-run deletes that group's tracks/vias first (verified:
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def refl(x, y): return 280.0 - x, 214.0 - y

# ------------------------------------------------------------------ placement tweaks (ESC1; ESC2 = reflection)
# low-side gate resistors move into the channel beside their FET gate (pad 2 next to pin 4); the DRV VM/VCP/CP caps
# are re-stacked on the DRV's right side (VM pins -> C320, VCP -> C317, CPH/CPL -> C316 below) so the top-side
# gate pins can escape; high-side gate resistors sit just outside the DRV escape fan.
MOVE1 = {
    'R311': (166.85, 66.0, 90), 'R313': (149.0, 66.0, 90), 'R315': (131.0, 66.0, 90),
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         'C431': (157.0, 128.0, 0), 'C441': (157.45, 129.7, 0), 'C442': (156.55, 126.3, 0), 'R416': (160.0, 128.0, 90), 'R419': (154.6, 128.65, 90),
         'R418': (157.0, 131.5, 0), 'R425': (156.1, 124.6, 0), 'R426': (159.65, 125.35, 0)}
# STM32: crystal load caps beside the crystal (C714 above OSC_OUT pad 3, C713 right of OSC_IN pad 1, C701 takes
# C713's old spot), VCAP2 cap into the free corner notch next to pin 73. The buck parts (incl. BOOT cap C528 and
# CZ cap C526) are placed by buckplace.py, run before this script.
MOVE3 = {'C713': (143.65, 107.95, 90), 'C714': (140.9, 104.45, 0), 'C701': (146.32, 107.63, 90), 'C712': (122.0, 114.95, 270)}
def place(ref, x, y, rot):
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    T = {}
    nm = lambda n: n if n == 'GND' else E + n
    # --- FET side (fixed): high-side gate via above pin 4, SH via in the phase gap beside source pin 3, low-side
    #     gate via under the channel resistor's pad 1 (phase C: none, GLC is on F.Cu); gate resistor pad 2 -> pin 4
    for ph, qh, ql, rh, rl, gh, sh, gl, rs, sp, sn in PHASES:
        x4, y4 = padxy(qh, '4'); x3, y3 = padxy(qh, '3'); xr, yr = padxy(rl, '1')
        T[f'VGH{ph}'] = (g5(x4), g5(y4 - 1.35)); T[f'VSH{ph}'] = (g5(x3 + 1.15), g5(y3)); T[f'VGL{ph}'] = (g5(xr), g5(yr + 1.45))
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        sgn = 1 if padxy(rs, '1')[0] > cx else -1
        xsp, xsn = round(cx + sgn * 0.45, 2), round(cx - sgn * 0.45, 2)
        add_track(E + f'SP{ph}', FCU, cx + sgn * 2.45, cy, xsp, cy, KW); add_track('GND', FCU, cx - sgn * 2.45, cy, xsn, cy, KW)
        if ph == 'B':      # SNB has to hop the SPB lane (pins are SP-left / SN-right, the shunt pads the other way)
            sp = R(E + f'SP{ph}', ('pt', xsp, cy, 0), ('pt', *END[f'SP{ph}'][0], 0), KW, tag=f'SP{ph}')
            R('GND', ('pt', xsn, cy, 0), ('pt', *gnd[ph], 0), KW, hug=sp, layers='FB', fnear=40, vd=0.5, tag=f'SN{ph}')
        elif ph == 'C':    # SNC (outer) keeps a lane free beside GLC for SPC, which then hugs SNC
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    R('/ESC_MCU/OSC_OUT', ('pad', 'Y701', '3'), ('pad', 'C714', '1'), 0.25, tag='C714')
    R('/ESC_MCU/OSC_IN', ('pad', 'Y701', '1'), ('pad', 'C713', '1'), 0.25, tag='C713')
    R('/ESC_MCU/VCAP1', ('pad', 'U701', '49'), ('pad', 'C711', '1'), 0.25, tag='VCAP1')
    # VCAP2 runs inside the pin row (under the package) so GND pin 74 and +3V3 pin 75 keep their outward exits
    poly('/ESC_MCU/VCAP2', [(122.6, 112.0), (123.5, 112.0), (123.5, 114.175), (122.3, 114.175)], 0.25); ROUTED.append(('VCAP2', 'poly'))
    # NRST crosses the crystal lines: one B.Cu hop
    R('/ESC_MCU/NRST', ('pad', 'U701', '14'), ('pad', 'C715', '1'), 0.25, layers='FB', fnear=2.0, vd=0.5, win=3.0, tag='NRST')
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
